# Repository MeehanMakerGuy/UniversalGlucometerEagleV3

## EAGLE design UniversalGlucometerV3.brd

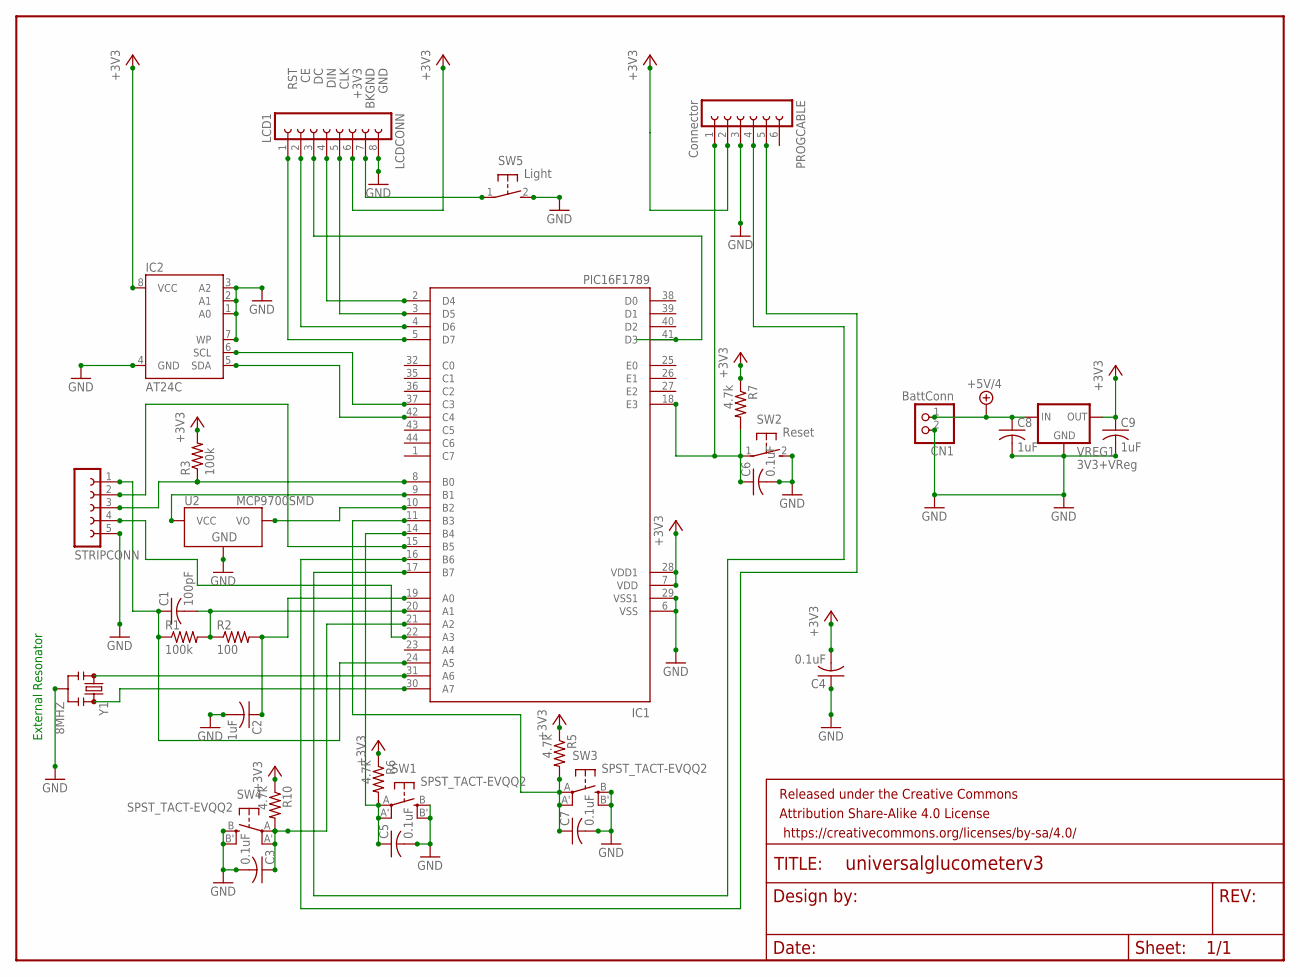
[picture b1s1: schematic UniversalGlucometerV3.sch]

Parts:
C1: 100pF; C0805
C2, C8, C9: 1uF; C0805
C3, C4, C5, C6, C7: 0.1uF; C0805
CN1: BattConn; JST-PH-2-THM-RA
FRAME1: FRAME-LETTER; CREATIVE_COMMONS
IC1: PIC16F1789; TQFP44
IC2: AT24C; SOIC8
LCDCONN: LCD1; FE08
PROGCABLE: Connector; FE06
R1, R3: 100k; R0805
R2: 100; R0805
R5, R6, R7, R10: 4.7k; R0805
STRIPCONN: FE05-1
SW1, SW3, SW4: SPST_TACT-EVQQ2; EVQ-Q2
SW2: Reset; B3F-31XX
SW5: Light; B3F-31XX
U2: MCP9700SMD; SOT23-3
VREG1: 3V3+VReg; SOT23-3
Y1: 8MHZ; RESONATOR-SMD

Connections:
+3V3: C4.2, C9.1, IC1.7 (VDD), IC1.28 (VDD1), IC2.8 (VCC), LCDCONN.6, PROGCABLE.2, R3.2, R5.1, R6.1, R7.1, R10.1, VREG1.2 (OUT)
+5V/4: C8.1, CN1.1 (2), VREG1.3 (IN)
BKGND: LCDCONN.7, SW5.1
CE: IC1.4 (D6), LCDCONN.2
CLK: IC1.3 (D5), LCDCONN.5
DC: IC1.41 (D3), LCDCONN.3
DIN: IC1.2 (D4), LCDCONN.4
GND: C2.2, C3.2, C4.1, C5.2, C6.2, C7.2, C8.2, C9.2, CN1.2 (1), IC1.6 (VSS), IC1.29 (VSS1), IC2.1 (A0), IC2.2 (A1), IC2.3 (A2), IC2.4 (GND), IC2.7 (WP), LCDCONN.8, PROGCABLE.3, STRIPCONN.5, SW1.B (S), SW1.B' (S1), SW2.2 (S), SW3.B (S), SW3.B' (S1), SW4.B (S), SW4.B' (S1), SW5.2 (S), U2.3 (GND), VREG1.1 (GND), Y1.2
unnamed: C6.1, IC1.18 (E3), PROGCABLE.1, R7.2, SW2.1
unnamed: IC1.9 (B1), U2.1 (VCC)
unnamed: IC1.15 (B5), STRIPCONN.2
unnamed: IC1.10 (B2), U2.2 (VO)
unnamed: C5.1, IC1.14 (B4), R6.2, SW1.A, SW1.A' (P1)
unnamed: IC1.8 (B0), R3.1, STRIPCONN.3
unnamed: C7.1, IC1.11 (B3), R5.2, SW3.A, SW3.A' (P1)
unnamed: C1.1, IC1.24 (A5), R1.1, STRIPCONN.1
unnamed: IC1.31 (A6), Y1.1
unnamed: IC1.37 (C3), IC2.6 (SCL)
unnamed: IC1.42 (C4), IC2.5 (SDA)
unnamed: IC1.30 (A7), Y1.3
unnamed: IC1.22 (A3), STRIPCONN.4
unnamed: C2.1, IC1.19 (A0), R2.2
unnamed: C3.1, IC1.21 (A2), R10.2, SW4.A, SW4.A' (P1)
unnamed: C1.2, IC1.20 (A1), R1.2, R2.1
unnamed: IC1.17 (B7), PROGCABLE.4
unnamed: IC1.16 (B6), PROGCABLE.5
RST: IC1.5 (D7), LCDCONN.1

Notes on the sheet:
External Resonator

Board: 2 copper layers, 31 parts (0 on the bottom side), 27 nets, no tracks yet.

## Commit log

2016-10-25 initial project version

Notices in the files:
parts and their libraries:
SparkFun-Aesthetics: Licensing: Creative Commons ShareAlike 4.0 International - https://creativecommons.org/licenses/by-sa/4.0
SparkFun-Aesthetics: Released under the Creative Commons Attribution Share-Alike 4.0 License
SparkFun-Aesthetics: https://creativecommons.org/licenses/by-sa/4.0
